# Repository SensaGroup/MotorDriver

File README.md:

# MotorDriver
SENSA MotorDriver is a board used for controlling main actuators on our robots on the Eurobot 2019 competition.

## Features
- 12V input with reverse polarity protection
- AT90CAN128
- 2x DC motor controllers
- 2x Stepper motor controllers
- 8x binary inputs
- 2x encoder inputs
- I2C/UART pinouts
- CAN Bus

## Pictures

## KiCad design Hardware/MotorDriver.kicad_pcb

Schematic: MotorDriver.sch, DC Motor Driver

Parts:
A1, A2: Pololu_Breakout_A4988; Pololu_Breakout-16_15.2x20.3mm
C1, C5, C9: 100n; C_0603_1608Metric
C2, C6, C16, C17: 47u; CP_Elec_6.3x5.4
C3, C4: 22p; C_0603_1608Metric
C7, C8: 10u; C_0805_2012Metric
C10, C11, C13, C14: 0.1u; C_0603_1608Metric
C12: 0.33u; C_0603_1608Metric
C15: 100u; CP_Elec_3x5.3
D1: LED1; LED_0603_1608Metric
D2: LED; LED_0603_1608Metric
D3: LED2; LED_0603_1608Metric
J1: Prog; PinHeader_1x06_P2.00mm_Vertical
J2: Conn_01x05; TerminalBlock_Phoenix_MPT-2.54mm_5pol
J3: SERIAL; Pin_Header_Straight_1x04_Pitch2.00mm
J4: MOTOROUTPUT; TerminalBlock_Phoenix_MKDS-3-4-5.08_1x04_P5.08mm_Horizontal
J5: I2C; Pin_Header_Straight_1x04_Pitch2.00mm
J6: ENCODER2; PinHeader_1x04_P2.54mm_Vertical
J7: perif_vcc; PinHeader_1x08_P2.54mm_Vertical
J8: ENCODER1; PinHeader_1x04_P2.54mm_Vertical
J9: perif_gnd; PinHeader_1x08_P2.54mm_Vertical
J10: perif_pins; PinHeader_1x08_P2.54mm_Vertical
J11: STEPPER1; TerminalBlock_TE_282834-4_1x04_P2.54mm_Horizontal
J12: STEPPER2; TerminalBlock_TE_282834-4_1x04_P2.54mm_Horizontal
MK1, MK2, MK3, MK4: Mounting_Hole; MountingHole_3.2mm_M3_DIN965_Pad
Q1: IPD068P03; TO-252-2
R1, R8, R9, R11: 10K; R_0603_1608Metric
R2, R3: 0.15/2W; R_2512_6332Metric
R4, R5, R6: 330; R_0603_1608Metric
R7, R10: 1K; R_0603_1608Metric
R12: R; R_0402_1005Metric
SW1: SW_DIP_x01; PinHeader_1x02_P1.00mm_Vertical
U1, U3: DRV8870DDA; Texas_HTSOP-8-1EP_3.9x4.9mm_P1.27mm_EP2.95x4.9mm_Mask2.4x3.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
U2: L7805; TO-252-2
U4: AT90CAN128-16AU; TQFP-64_14x14mm_P0.8mm
U5: MCP2551-I-SN; SOIC-8_3.9x4.9mm_P1.27mm
Y1: OSCILLATOR-16MHZ; Oscillator_SMD_Abracon_ASE-4pin_3.2x2.5mm

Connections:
+5V: A1.2 (VDD), A2.2 (VDD), C5.1, C9.1, C14.1, D2.2 (A), J1.1, J3.1, J5.1, J6.1, J7.1, J7.2, J7.3, J7.4, J7.5, J7.6, J7.7, J7.8, J8.1, R1.1, R7.1, R8.1, R9.1, R10.1, R12.1, U1.4 (VREF), U3.4 (VREF), U4.21 (VCC), U4.52 (VCC), U4.62 (AREF), U4.64 (AVCC), U5.3 (VDD)
CANH: J2.4, U5.7 (CANH)
CANL: J2.5, U5.6 (CANL)
CAN_RX: R10.2, U4.31 (PD6), U5.4 (RXD)
CAN_TX: R7.2, U4.30 (PD5), U5.1 (TXD)
ENC1_A: J8.2, U4.27 (PD2)
ENC1_B: J8.3, U4.28 (PD3)
ENC2_A: J6.2, U4.8 (PE6)
ENC2_B: J6.3, U4.9 (PE7)
F0: J10.1, U4.61 (PF0)
F1: J10.2, U4.60 (PF1)
F2: J10.3, U4.59 (PF2)
F3: J10.4, U4.58 (PF3)
F4: J10.5, U4.57 (PF4)
F5: J10.6, U4.56 (PF5)
F6: J10.7, U4.55 (PF6)
F7: J10.8, U4.54 (PF7)
GND: A1.1 (GND), A1.7 (GND), A2.1 (GND), A2.7 (GND), C1.2, C2.2, C3.2, C4.2, C5.2, C6.2, C7.2, C8.2, C9.2, C10.2, C11.2, C12.2, C13.2, C14.2, C15.2, C16.2, C17.2, J1.6, J2.2, J2.3, J3.4, J5.2, J6.4, J8.4, J9.1, J9.2, J9.3, J9.4, J9.5, J9.6, J9.7, J9.8, Q1.1 (G), R2.2, R3.2, R4.2, R5.2, R6.2, R11.2, SW1.2, U1.1 (GND), U1.9 (GND), U2.2 (GND), U3.1 (GND), U3.9 (GND), U4.22 (GND), U4.53 (GND), U4.63 (AGND), U5.2 (VSS)
INPUT_VCC: J2.1, Q1.2 (D)
LED1: D1.2 (A), U4.33 (PG0)
LED2: D3.2 (A), U4.34 (PG1)
MTR11: U1.3 (IN1), U4.5 (PE3)
MTR12: U1.2 (IN2), U4.6 (PE4)
MTR21: U3.3 (IN1), U4.7 (PE5)
MTR22: U3.2 (IN2), U4.17 (PB7)
MTROUT_11: J4.4, U1.6 (OUT1)
MTROUT_12: J4.3, U1.8 (OUT2)
MTROUT_21: J4.2, U3.6 (OUT1)
MTROUT_22: J4.1, U3.8 (OUT2)
unnamed: A1.3 (1B), J11.1
unnamed: A1.4 (1A), J11.2
unnamed: A1.5 (2A), J11.3
unnamed: A1.6 (2B), J11.4
unnamed: A1.13 (~RESET), A1.14 (~SLEEP)
unnamed: A2.3 (1B), J12.1
unnamed: A2.4 (1A), J12.2
unnamed: A2.5 (2A), J12.3
unnamed: A2.6 (2B), J12.4
unnamed: A2.13 (~RESET), A2.14 (~SLEEP)
unnamed: C13.1, R12.2, U2.3 (OUT)
unnamed: D1.1 (K), R4.1
unnamed: D2.1 (K), R5.1
unnamed: D3.1 (K), R6.1
unnamed: R2.1, U1.7 (ISEN)
unnamed: R3.1, U3.7 (ISEN)
unnamed: R11.1, U5.8 (Rs)
RESET: C1.1, J1.5, R1.2, SW1.1, U4.20 (~RESET)
RXD0: J1.2, J3.2, U4.2 (PE0)
SCK: J1.4, U4.11 (PB1)
SCL: J5.4, R9.2, U4.25 (PD0)
SDA: J5.3, R8.2, U4.26 (PD1)
STP1_DIR: A1.16 (DIR), U4.35 (PC0)
STP1_ENABLE: A1.9 (~ENABLE), U4.37 (PC2)
STP1_STEP: A1.15 (STEP), U4.36 (PC1)
STP2_DIR: A2.16 (DIR), U4.38 (PC3)
STP2_ENABLE: A2.9 (~ENABLE), U4.40 (PC5)
STP2_STEP: A2.15 (STEP), U4.39 (PC4)
TXD0: J1.3, J3.3, U4.3 (PE1)
VCC: A1.8 (VMOT), A2.8 (VMOT), C2.1, C6.1, C7.1, C8.1, C10.1, C11.1, C12.1, C15.1, C16.1, C17.1, Q1.3 (S), U1.5 (VM), U2.1 (IN), U3.5 (VM)
XTAL1: C4.1, U4.24 (XTAL1), Y1.1
XTAL2: C3.1, U4.23 (XTAL2), Y1.3

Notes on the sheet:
OSCILLATOR 16MHz
UART
I2C
I2C pullup
RESET
INT2
INT3
INT6
INT7
expected AMT102, but works with other
Not fitted
INPUT TERMINAL
ENCODER
REGULATOR 5V
INPUT PROTECTION
PERIF. PINS
DEBUG LED
MCP2551 CAN TRANSCEIVER
2x DRV8870
PROG. PORT
MOUNTING HOLE
AT90CAN128
A4988 MODULES

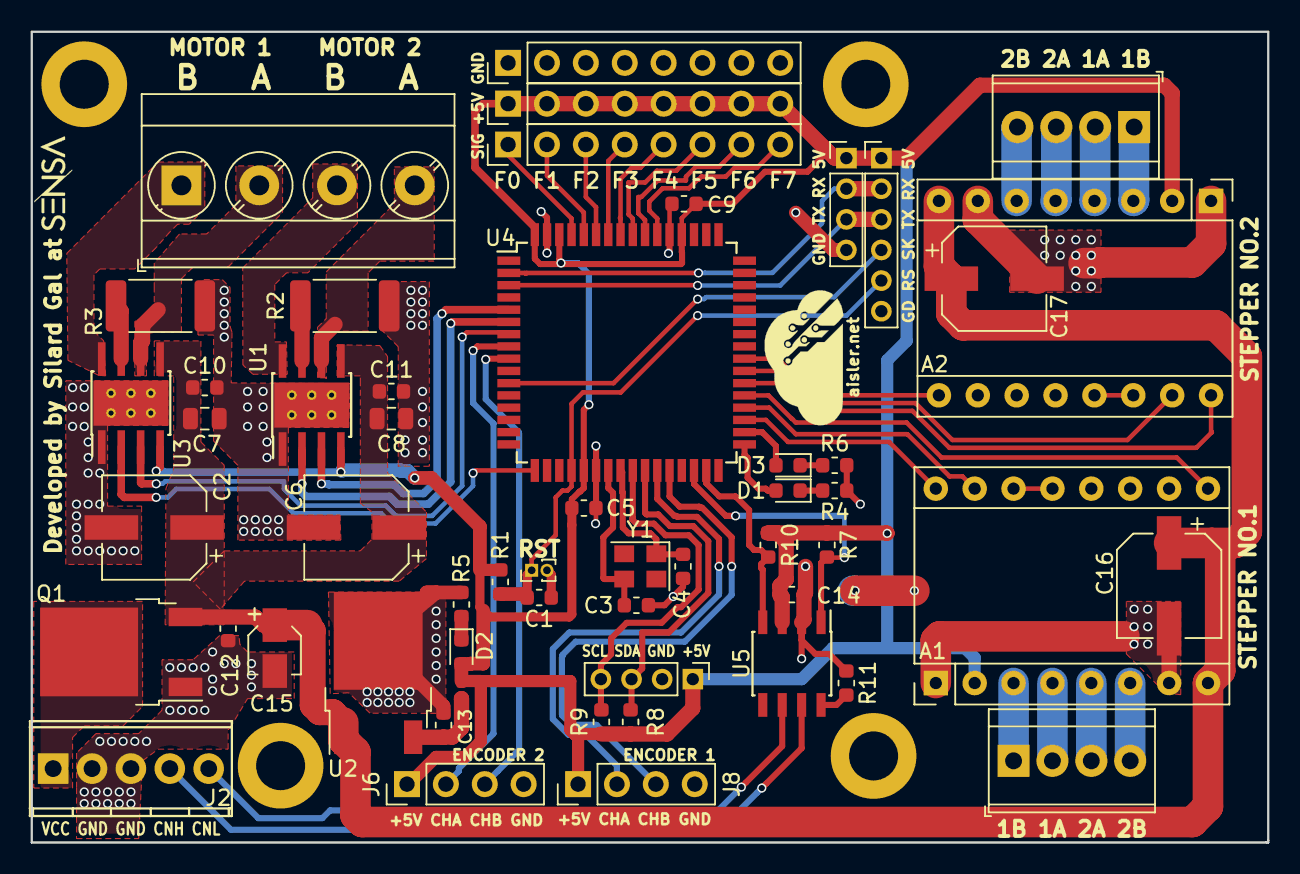
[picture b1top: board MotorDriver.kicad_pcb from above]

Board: 2 copper layers, 80.8 x 53.0 mm, 58 parts (0 on the bottom side), 61 nets.

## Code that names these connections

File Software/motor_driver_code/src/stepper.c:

#include "stepper.h"

static unsigned int stepper_rpm[2] = {60, 60};

#define PIN_STEPPER1_DIR            16  // PC0
#define PIN_STEPPER1_STEP           17  // PC1
#define PIN_STEPPER1_EN             18  // PC2

#define PIN_STEPPER2_DIR            19  // PC3
#define PIN_STEPPER2_STEP           20  // PC4
#define PIN_STEPPER2_EN             21  // PC5

#define rtn_dir(num) (num == 1)? PIN_STEPPER1_DIR: PIN_STEPPER2_DIR
#define rtn_step(num) (num == 1)? PIN_STEPPER1_STEP: PIN_STEPPER2_STEP
#define rtn_en(num) (num == 1)? PIN_STEPPER1_EN: PIN_STEPPER2_EN

/*
 * Function:    unsigned char init_stepper()
 * Description: init the stepper pins
 */
unsigned char init_stepper(void) {
    
    gpio_register_pin(PIN_STEPPER1_DIR, GPIO_DIRECTION_OUTPUT, false);
    gpio_register_pin(PIN_STEPPER1_STEP, GPIO_DIRECTION_OUTPUT, false);
    gpio_register_pin(PIN_STEPPER1_EN, GPIO_DIRECTION_OUTPUT, false);

    gpio_register_pin(PIN_STEPPER2_DIR, GPIO_DIRECTION_OUTPUT, false);
    gpio_register_pin(PIN_STEPPER2_STEP, GPIO_DIRECTION_OUTPUT, false);
    gpio_register_pin(PIN_STEPPER2_EN, GPIO_DIRECTION_OUTPUT, false);

    // disable drivers
    /*enable_stepper(HIGH, 1);
    enable_stepper(HIGH, 2);*/

    return 1;

} // end of init_stepper()

/*
 *  Function:       void enable_stepper(uint8_t state, uint8_t num)
 *  Description:    enable or disable the stepper driver
 */
void enable_stepper(uint8_t state, uint8_t num) {

    gpio_write_pin(rtn_en(num), state);

} // end of enable_stepper()

/*
 * Function:        void set_rpm_stepper(unsigned int rpm, uint8_t num)
 * Description:     set the rpm of the stepper
 */
void set_rpm_stepper(unsigned int rpm, uint8_t num) {

    stepper_rpm[num-1] = rpm;

} // end of set_rpm_stepper()

/*
 * Function: void move_stepper(unsigned int steps, unsigned char dir, uint8_t num)
 * Description: move the stepper for steps at a certain direction 
 */
void move_stepper(unsigned int steps, unsigned char dir, uint8_t num) {
    /*

    Delay between each step for the rpm and step:
    60000/(RPM*STEP) = x, where x is the time between each step

    */
    int time_calculate = 60000 / (stepper_rpm[num-1] * steps);

    gpio_write_pin(rtn_dir(num), dir);

    for(unsigned int i=0; i<steps; i++) {
        gpio_write_pin(rtn_step(num), ON);
        delay(time_calculate/2);
        gpio_write_pin(rtn_step(num), OFF);
        delay(time_calculate/2);
    }
} // end of move_stepper()

// add encoder support here

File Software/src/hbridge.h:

#ifndef _HBRIDGE_H_
#define _HBRIDGE_H_

#include <avr/io.h>
#include <util/delay.h>
#include "system.h"

#define PIN_MOTOR1_A 35 // PE3
#define PIN_MOTOR1_B 36 // PE4
#define PIN_MOTOR2_A 37 // PE5
#define PIN_MOTOR2_B 15 // PB7

#define conv_to_16(x) ((65535*x) / 100)
#define conv_from_16(x) ((x/65535)*100)

#define conv_to_8(x)  ((255*x) / 100)
#define conv_from_8(x) ((x/255) * 100)

unsigned char init_hbridge(void);
void hbridge_move(int A_value, int B_value, uint8_t num);
void hbridge_break(uint8_t num);
void hbridge_time(int num, int dir, int achieve, int time);

#endif

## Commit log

2018-11-23 Main files
2018-11-23 Small change in readme for software
2018-12-19 LED, UART, Switches and DC working. Stepper needs testing and CAN Bus
2018-12-19 Readme updated
2019-03-18 CAN Bus working with 100kbps
2019-03-18 Added full communication, needs testing
2019-03-22 Steppers should work fine now
2019-03-26 Readme and pictures
2019-03-26 Picture
